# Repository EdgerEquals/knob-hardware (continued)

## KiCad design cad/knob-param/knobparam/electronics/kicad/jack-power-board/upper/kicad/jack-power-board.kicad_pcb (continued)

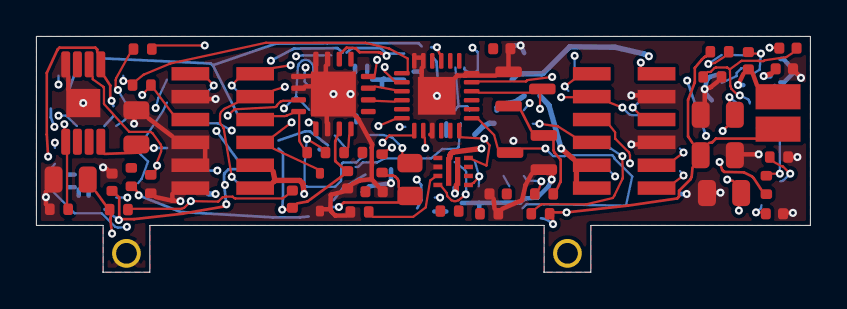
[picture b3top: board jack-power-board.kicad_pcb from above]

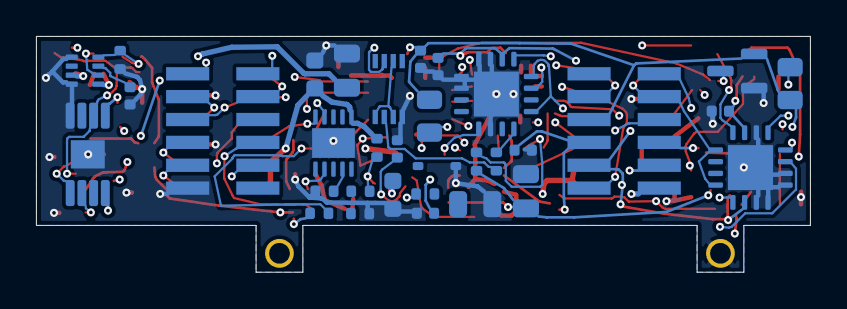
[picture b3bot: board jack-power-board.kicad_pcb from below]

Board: 4 copper layers, 43.0 x 13.1 mm, 79 parts (33 on the bottom side), 68 nets.

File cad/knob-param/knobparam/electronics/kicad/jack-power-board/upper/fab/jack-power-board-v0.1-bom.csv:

Item,Designator,Qty,Value,Footprint,Manufacturer,MPN,LCSC
1,"C20,C25",2,10nF 25V,C_0402_1005Metric,,,
2,"C22,C24",2,4.7uF 50V,C_0805_2012Metric,,,
3,"C10,C23,C27,C30",4,10uF 25V,C_0805_2012Metric,,,
4,"C21,C26,C29",3,10nF,C_0402_1005Metric,,,
5,C31,1,100nF 50V,C_0402_1005Metric,,,
6,"C32,C33",2,22uF 10V,C_0805_2012Metric,,,
7,"C53,C60",2,100nF,C_0402_1005Metric,,,
8,"C28,C54,C55,C56,C57,C58,C59",7,100nF 25V,C_0402_1005Metric,,,
9,C7,1,1nF 25V,C_0402_1005Metric,,,
10,C8,1,2.2nF,C_0402_1005Metric,,,
11,"C6,C9",2,1uF 50V,C_0603_1608Metric,,,
12,"D1,D2",2,PESD24VL1BA,D_SOD-323,,"PESD24VL1BA,115",C69324
13,"D5,D6,D7",3,BAV99,SOT-23,,BAV99,C2500
14,"H1,H2",2,PM127VS-12-12-H34,PinSocket_2x06_P1.27mm_Vertical_SMD,,PM127VS-12-12-H34-4.5-R,C2840010
15,"H3,H4",2,PZ127VS-12-12-H16,PinHeader_2x06_P1.27mm_Vertical_SMD,,PZ127VS-12-12-H16-4.5-R,C2840009
16,L2,1,2.2uH 1A,L_Cenker_CKCS252012,,,
17,R13,1,95.3k 0.5%,R_0402_1005Metric,,,
18,"R14,R16",2,10.0k 0.5%,R_0402_1005Metric,,,
19,R15,1,93.1k 0.5%,R_0402_1005Metric,,,
20,R17,1,30.9k,R_0402_1005Metric,,,
21,R2,1,14.0k,R_0402_1005Metric,,,
22,R3,1,22.6k,R_0402_1005Metric,,,
23,R4,1,102k,R_0402_1005Metric,,,
24,"R43,R45,R47",3,10R,R_0402_1005Metric,,,
25,"R44,R46,R48",3,33R 0.5W,R_0805_2012Metric,,,
26,"R49,R51,R53,R58,R59",5,100k,R_0402_1005Metric,,,
27,R5,1,30.1k,R_0402_1005Metric,,,
28,"R50,R52,R54",3,470k,R_0402_1005Metric,,,
29,"R55,R56",2,4.7k,R_0402_1005Metric,,,
30,"R18,R6",2,10.0k,R_0402_1005Metric,,,
31,"R57,R60",2,10k,R_0402_1005Metric,,,
32,R7,1,1.00k,R_0402_1005Metric,,,
33,U1,1,HUSB238_002DD,DFN-10-1EP_3x3mm_P0.5mm_EP1.65x2.38mm,,HUSB238_002DD,C7471904
34,U10,1,SN74LVC3G07DCUR,VSSOP-8_2.3x2mm_P0.5mm,,SN74LVC3G07DCUR,C131955
35,"U11,U12,U13",3,TMUX7212RUMR,QFN-16-1EP_4x4mm_P0.65mm_EP2.5x2.5mm,,TMUX7212RUMR,C3657300
36,U14,1,TCA9535RGER,Texas_RGE0024C_VQFN-24-1EP_4x4mm_P0.5mm_EP2.1x2.1mm,,TCA9535RGER,C527428
37,U2,1,TPS259470ARPWR,TI_RPW0010A_VQFN-HR-10_2x2_PLACEHOLDER,,TPS259470ARPWR,C3662799
38,U4,1,TPS7A4901DGNR,HVSSOP-8-1EP_3x3mm_P0.65mm_EP1.57x1.89mm,,TPS7A4901DGNR,C16430
39,U5,1,TPS7A3001DGNR,HVSSOP-8-1EP_3x3mm_P0.65mm_EP1.57x1.89mm,,TPS7A3001DGNR,C33835
40,U6,1,TPS62933FDRLR,SOT-583-8,,TPS62933FDRLR,C5219272

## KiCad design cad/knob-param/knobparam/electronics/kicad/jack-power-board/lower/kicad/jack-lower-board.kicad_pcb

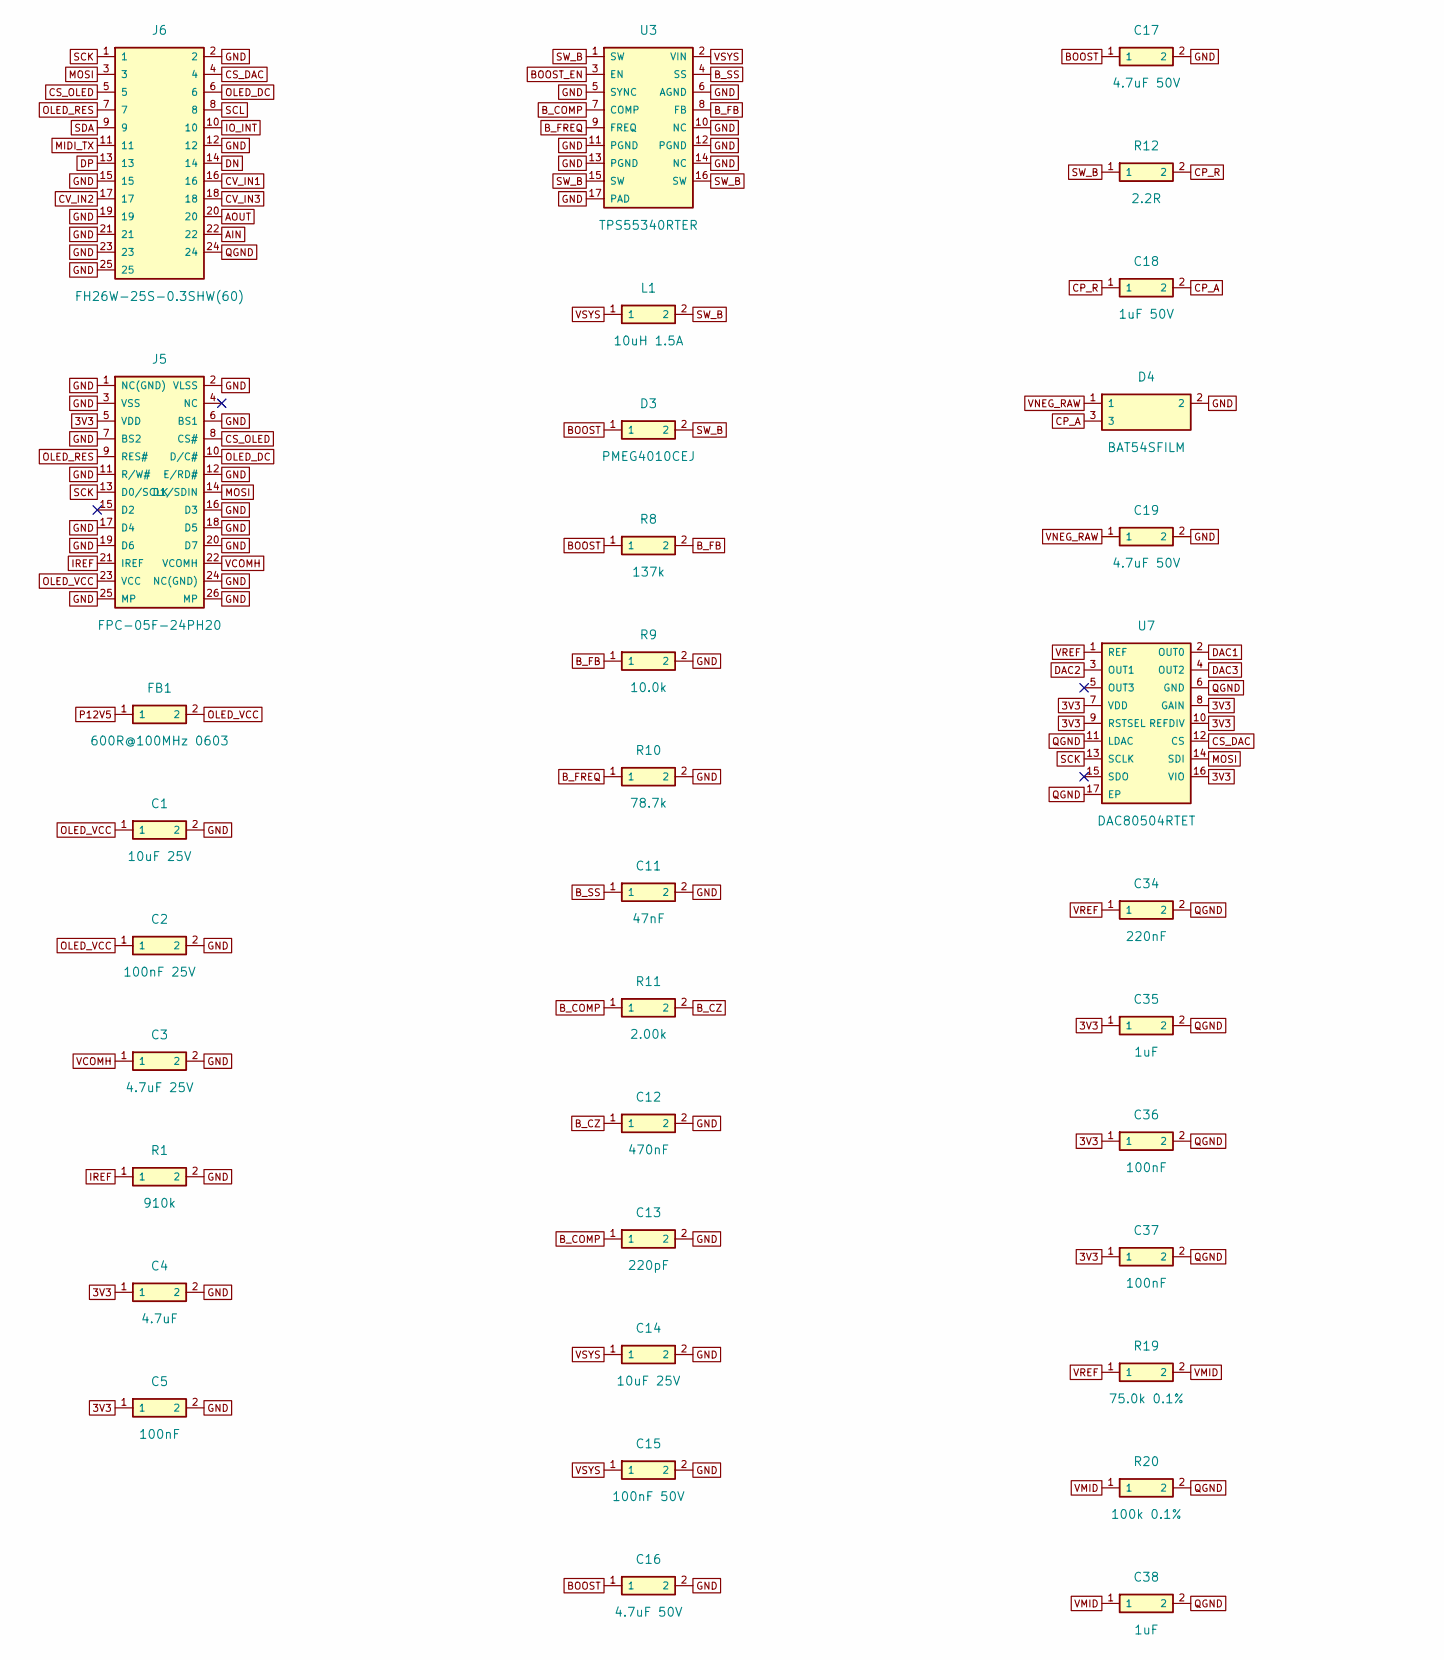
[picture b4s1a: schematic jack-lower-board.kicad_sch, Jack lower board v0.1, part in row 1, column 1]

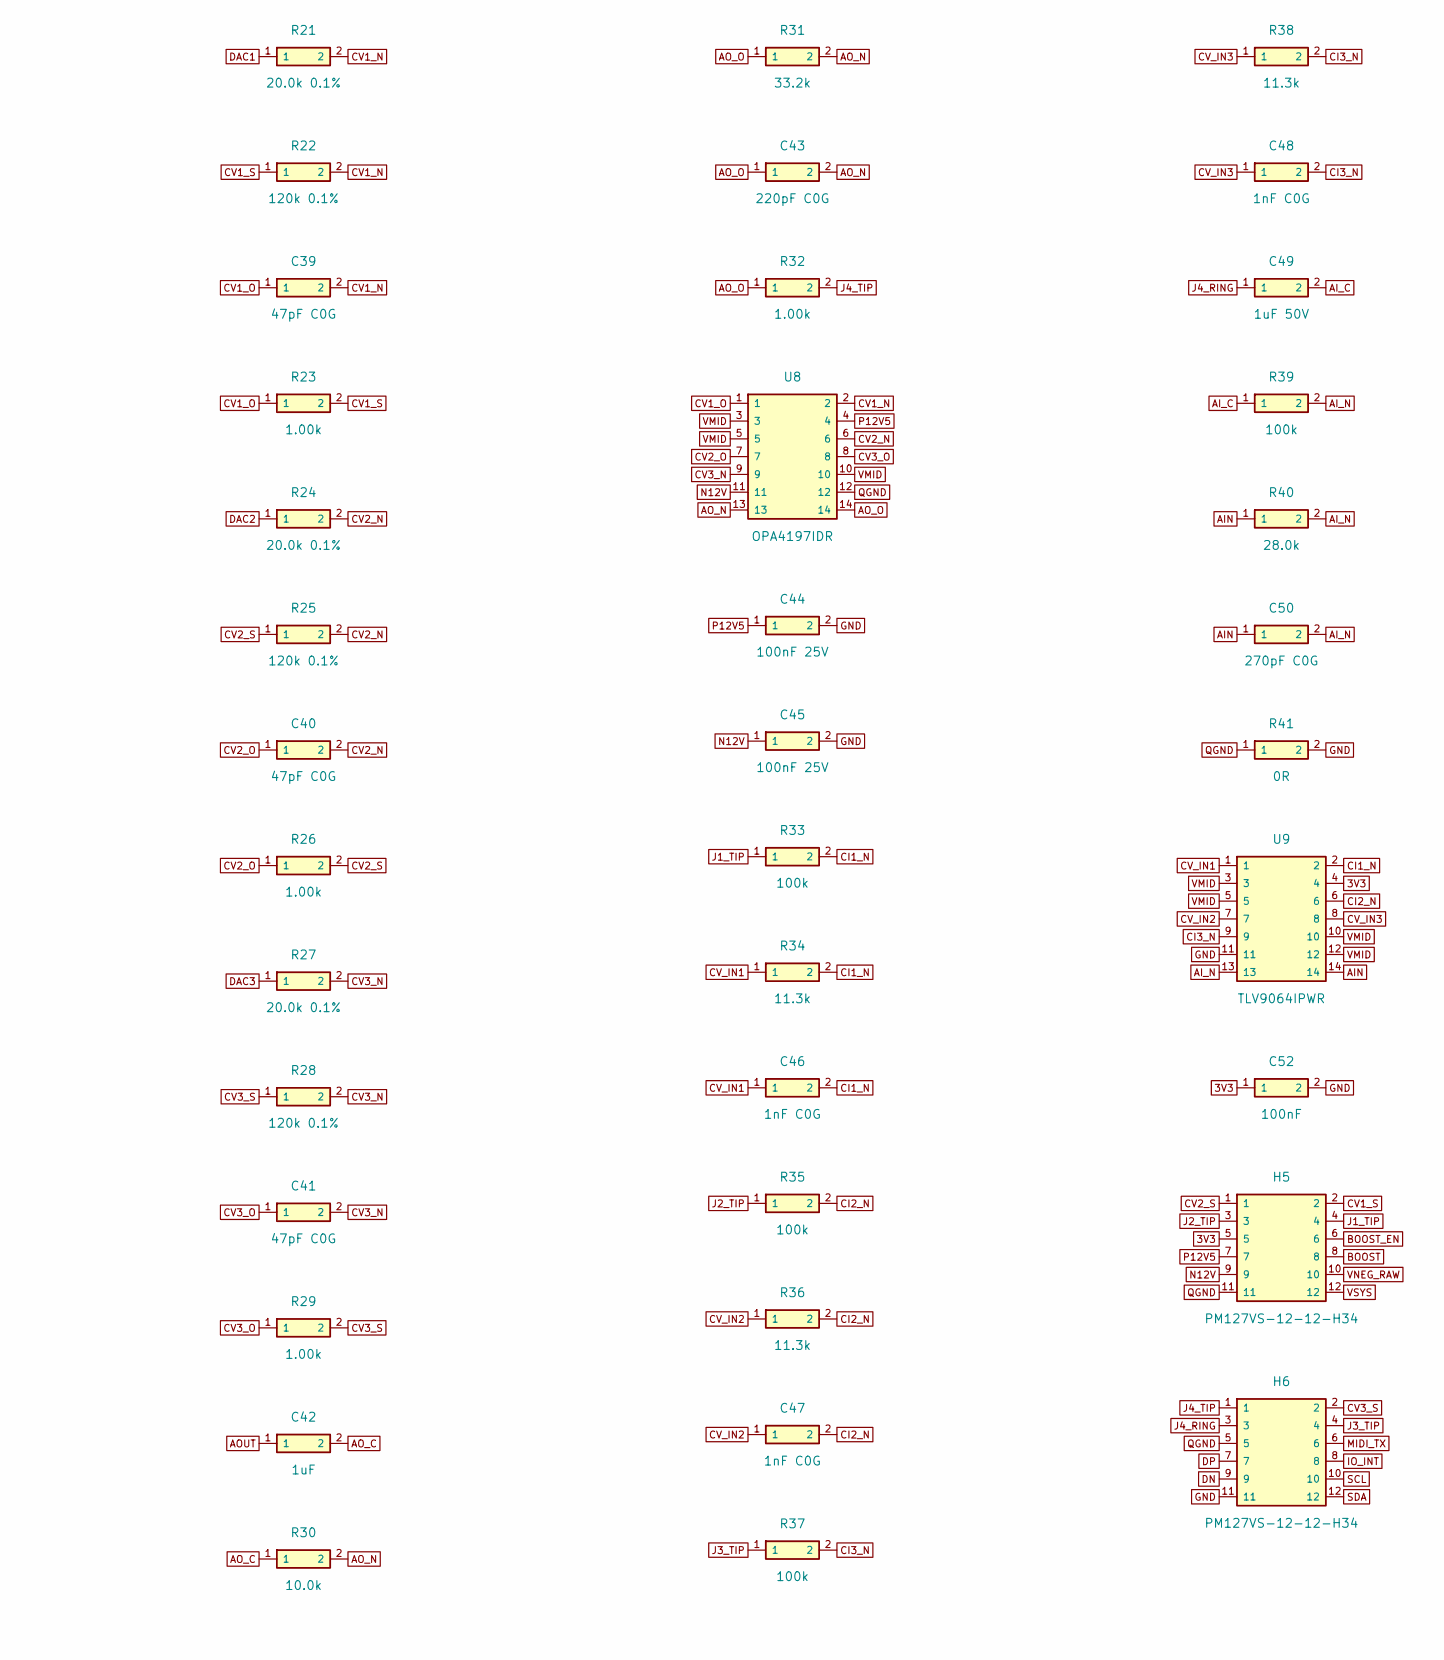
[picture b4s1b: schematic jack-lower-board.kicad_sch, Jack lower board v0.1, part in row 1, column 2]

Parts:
C1, C14: 10uF 25V; C_0805_2012Metric
C2, C44, C45: 100nF 25V; C_0402_1005Metric
C3: 4.7uF 25V; C_0805_2012Metric
C4: 4.7uF; C_0603_1608Metric
C5, C36, C37, C52: 100nF; C_0402_1005Metric
C11: 47nF; C_0402_1005Metric
C12: 470nF; C_0402_1005Metric
C13: 220pF; C_0402_1005Metric
C15: 100nF 50V; C_0402_1005Metric
C16, C17, C19: 4.7uF 50V; C_0805_2012Metric
C18, C49: 1uF 50V; C_0603_1608Metric
C34: 220nF; C_0402_1005Metric
C35, C38, C42: 1uF; C_0402_1005Metric
C39, C40, C41: 47pF C0G; C_0402_1005Metric
C43: 220pF C0G; C_0402_1005Metric
C46, C47, C48: 1nF C0G; C_0402_1005Metric
C50: 270pF C0G; C_0402_1005Metric
D3: PMEG4010CEJ; D_SOD-323F; MPN PMEG4010CEJ,115; LCSC C50704
D4: BAT54SFILM; SOT-23; MPN BAT54SFILM; LCSC C377935
FB1: 600R@100MHz 0603; L_0603_1608Metric
H5, H6: PM127VS-12-12-H34; PinSocket_2x06_P1.27mm_Vertical_SMD; MPN PM127VS-12-12-H34-4.5-R; LCSC C2840010
J5: FPC-05F-24PH20; XUNPU_FPC-05F-24PH20; MPN FPC-05F-24PH20; LCSC C2856805
J6: FH26W-25S-0.3SHW(60); Hirose_FH26-25S-0.3SHW_2Rows-25Pins-1MP_P0.60mm_Horizontal; MPN FH26W-25S-0.3SHW(60); LCSC C2904698
L1: 10uH 1.5A; L_Cenker_CKCS4020
R1: 910k; R_0402_1005Metric
R8: 137k; R_0402_1005Metric
R9, R30: 10.0k; R_0402_1005Metric
R10: 78.7k; R_0402_1005Metric
R11: 2.00k; R_0402_1005Metric
R12: 2.2R; R_0603_1608Metric
R19: 75.0k 0.1%; R_0402_1005Metric
R20: 100k 0.1%; R_0402_1005Metric
R21, R24, R27: 20.0k 0.1%; R_0402_1005Metric
R22, R25, R28: 120k 0.1%; R_0402_1005Metric
R23, R26, R29, R32: 1.00k; R_0402_1005Metric
R31: 33.2k; R_0402_1005Metric
R33, R35, R37, R39: 100k; R_0402_1005Metric
R34, R36, R38: 11.3k; R_0402_1005Metric
R40: 28.0k; R_0402_1005Metric
R41: 0R; R_0402_1005Metric
U3: TPS55340RTER; QFN-16-1EP_3x3mm_P0.5mm_EP1.7x1.7mm; MPN TPS55340RTER; LCSC C169167
U7: DAC80504RTET; QFN-16-1EP_3x3mm_P0.5mm_EP1.7x1.7mm; MPN DAC80504RTET; LCSC C2862796
U8: OPA4197IDR; SOIC-14_3.9x8.7mm_P1.27mm; MPN OPA4197IDR; LCSC C2058532
U9: TLV9064IPWR; TSSOP-14_4.4x5mm_P0.65mm; MPN TLV9064IPWR; LCSC C779410

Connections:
3V3: C4.1, C5.1, C35.1, C36.1, C37.1, C52.1, H5.5, J5.5 (VDD), U7.7 (VDD), U7.8 (GAIN), U7.9 (RSTSEL), U7.10 (REFDIV), U7.16 (VIO), U9.4
AIN: C50.1, J6.22, R40.1, U9.14
AI_C: C49.2, R39.1
AI_N: C50.2, R39.2, R40.2, U9.13
AOUT: C42.1, J6.20
AO_C: C42.2, R30.1
AO_N: C43.2, R30.2, R31.2, U8.13
AO_O: C43.1, R31.1, R32.1, U8.14
BOOST: C16.1, C17.1, D3.1, H5.8, R8.1
BOOST_EN: H5.6, U3.3 (EN)
B_COMP: C13.1, R11.1, U3.7 (COMP)
B_CZ: C12.1, R11.2
B_FB: R8.2, R9.1, U3.8 (FB)
B_FREQ: R10.1, U3.9 (FREQ)
B_SS: C11.1, U3.4 (SS)
CI1_N: C46.2, R33.2, R34.2, U9.2
CI2_N: C47.2, R35.2, R36.2, U9.6
CI3_N: C48.2, R37.2, R38.2, U9.9
CP_A: C18.2, D4.3
CP_R: C18.1, R12.2
CS_DAC: J6.4, U7.12 (CS)
CS_OLED: J5.8 (CS#), J6.5
CV1_N: C39.2, R21.2, R22.2, U8.2
CV1_O: C39.1, R23.1, U8.1
CV1_S: H5.2, R22.1, R23.2
CV2_N: C40.2, R24.2, R25.2, U8.6
CV2_O: C40.1, R26.1, U8.7
CV2_S: H5.1, R25.1, R26.2
CV3_N: C41.2, R27.2, R28.2, U8.9
CV3_O: C41.1, R29.1, U8.8
CV3_S: H6.2, R28.1, R29.2
CV_IN1: C46.1, J6.16, R34.1, U9.1
CV_IN2: C47.1, J6.17, R36.1, U9.7
CV_IN3: C48.1, J6.18, R38.1, U9.8
DAC1: R21.1, U7.2 (OUT0)
DAC2: R24.1, U7.3 (OUT1)
DAC3: R27.1, U7.4 (OUT2)
DN: H6.9, J6.14
DP: H6.7, J6.13
GND: C1.2, C2.2, C3.2, C4.2, C5.2, C11.2, C12.2, C13.2, C14.2, C15.2, C16.2, C17.2, C19.2, C44.2, C45.2, C52.2, D4.2, H6.11, J5.1 (NC(GND)), J5.2 (VLSS), J5.3 (VSS), J5.6 (BS1), J5.7 (BS2), J5.11 (R/W#), J5.12 (E/RD#), J5.16 (D3), J5.17 (D4), J5.18 (D5), J5.19 (D6), J5.20 (D7), J5.24 (NC(GND)), J5.25 (MP), J5.26 (MP), J6.2, J6.12, J6.15, J6.19, J6.21, J6.23, J6.25, R1.2, R9.2, R10.2, R41.2, U3.5 (SYNC), U3.6 (AGND), U3.10 (NC), U3.11 (PGND), U3.12 (PGND), U3.13 (PGND), U3.14 (NC), U3.17 (PAD), U9.11
IO_INT: H6.8, J6.10
IREF: J5.21 (IREF), R1.1
J1_TIP: H5.4, R33.1
J2_TIP: H5.3, R35.1
J3_TIP: H6.4, R37.1
J4_RING: C49.1, H6.3
J4_TIP: H6.1, R32.2
MIDI_TX: H6.6, J6.11
MOSI: J5.14 (D1/SDIN), J6.3, U7.14 (SDI)
N12V: C45.1, H5.9, U8.11
OLED_DC: J5.10 (D/C#), J6.6
OLED_RES: J5.9 (RES#), J6.7
OLED_VCC: C1.1, C2.1, FB1.2, J5.23 (VCC)
P12V5: C44.1, FB1.1, H5.7, U8.4
QGND: C34.2, C35.2, C36.2, C37.2, C38.2, H5.11, H6.5, J6.24, R20.2, R41.1, U7.6 (GND), U7.11 (LDAC), U7.17 (EP), U8.12
SCK: J5.13 (D0/SCLK), J6.1, U7.13 (SCLK)
SCL: H6.10, J6.8
SDA: H6.12, J6.9
SW_B: D3.2, L1.2, R12.1, U3.1 (SW), U3.15 (SW), U3.16 (SW)
VCOMH: C3.1, J5.22 (VCOMH)
VMID: C38.1, R19.2, R20.1, U8.3, U8.5, U8.10, U9.3, U9.5, U9.10, U9.12
VNEG_RAW: C19.1, D4.1, H5.10
VREF: C34.1, R19.1, U7.1 (REF)
VSYS: C14.1, C15.1, H5.12, L1.1, U3.2 (VIN)

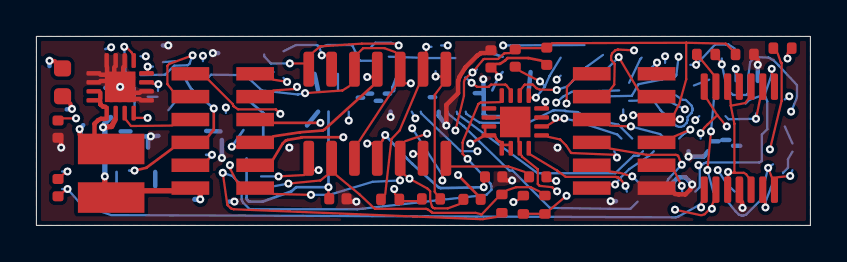
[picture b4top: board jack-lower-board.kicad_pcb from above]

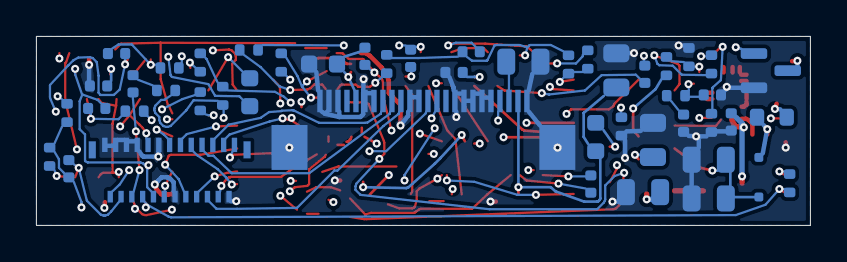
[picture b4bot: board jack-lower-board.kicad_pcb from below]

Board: 4 copper layers, 43.0 x 10.5 mm, 73 parts (48 on the bottom side), 64 nets.

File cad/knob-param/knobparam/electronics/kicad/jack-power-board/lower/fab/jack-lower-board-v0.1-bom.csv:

Item,Designator,Qty,Value,Footprint,Manufacturer,MPN,LCSC
1,"C1,C14",2,10uF 25V,C_0805_2012Metric,,,
2,C11,1,47nF,C_0402_1005Metric,,,
3,C12,1,470nF,C_0402_1005Metric,,,
4,C13,1,220pF,C_0402_1005Metric,,,
5,C15,1,100nF 50V,C_0402_1005Metric,,,
6,"C16,C17,C19",3,4.7uF 50V,C_0805_2012Metric,,,
7,"C18,C49",2,1uF 50V,C_0603_1608Metric,,,
8,C3,1,4.7uF 25V,C_0805_2012Metric,,,
9,C34,1,220nF,C_0402_1005Metric,,,
10,"C35,C38,C42,C51",4,1uF,C_0402_1005Metric,,,
11,"C36,C37,C5,C52",4,100nF,C_0402_1005Metric,,,
12,C4,1,4.7uF,C_0603_1608Metric,,,
13,"C39,C40,C41",3,47pF C0G,C_0402_1005Metric,,,
14,"C43,C50",2,220pF C0G,C_0402_1005Metric,,,
15,"C2,C44,C45",3,100nF 25V,C_0402_1005Metric,,,
16,"C46,C47,C48",3,1nF C0G,C_0402_1005Metric,,,
17,D3,1,PMEG4010CEJ,D_SOD-323F,,"PMEG4010CEJ,115",C50704
18,D4,1,BAT54SFILM,SOT-23,,BAT54SFILM,C377935
19,FB1,1,600R@100MHz 0603,L_0603_1608Metric,,,
20,"H5,H6",2,PM127VS-12-12-H34,PinSocket_2x06_P1.27mm_Vertical_SMD,,PM127VS-12-12-H34-4.5-R,C2840010
21,J5,1,FPC-05F-24PH20,XUNPU_FPC-05F-24PH20,,FPC-05F-24PH20,C2856805
22,J6,1,FH26W-25S-0.3SHW(60),Hirose_FH26-25S-0.3SHW_2Rows-25Pins-1MP_P0.60mm_Horizontal,,FH26W-25S-0.3SHW(60),C2904698
23,L1,1,10uH 1.5A,L_Cenker_CKCS4020,,,
24,R1,1,910k,R_0402_1005Metric,,,
25,R10,1,78.7k,R_0402_1005Metric,,,
26,R11,1,2.00k,R_0402_1005Metric,,,
27,R12,1,2.2R,R_0603_1608Metric,,,
28,R19,1,75.0k 0.1%,R_0402_1005Metric,,,
29,R20,1,100k 0.1%,R_0402_1005Metric,,,
30,"R22,R25,R28",3,120k 0.1%,R_0402_1005Metric,,,
31,"R21,R24,R27",3,20.0k 0.1%,R_0402_1005Metric,,,
32,"R23,R26,R29,R32",4,1.00k,R_0402_1005Metric,,,
33,R31,1,30.1k,R_0402_1005Metric,,,
34,"R34,R36,R38",3,13.3k,R_0402_1005Metric,,,
35,"R33,R35,R37,R39",4,100k,R_0402_1005Metric,,,
36,R40,1,33.0k,R_0402_1005Metric,,,
37,"R30,R41,R42,R9",4,10.0k,R_0402_1005Metric,,,
38,R8,1,137k,R_0402_1005Metric,,,
39,U3,1,TPS55340RTER,QFN-16-1EP_3x3mm_P0.5mm_EP1.7x1.7mm,,TPS55340RTER,C169167
40,U7,1,DAC80504RTET,QFN-16-1EP_3x3mm_P0.5mm_EP1.7x1.7mm,,DAC80504RTET,C2862796
41,U8,1,OPA4197IDR,SOIC-14_3.9x8.7mm_P1.27mm,,OPA4197IDR,C2058532
42,U9,1,TLV9064IPWR,TSSOP-14_4.4x5mm_P0.65mm,,TLV9064IPWR,C779410

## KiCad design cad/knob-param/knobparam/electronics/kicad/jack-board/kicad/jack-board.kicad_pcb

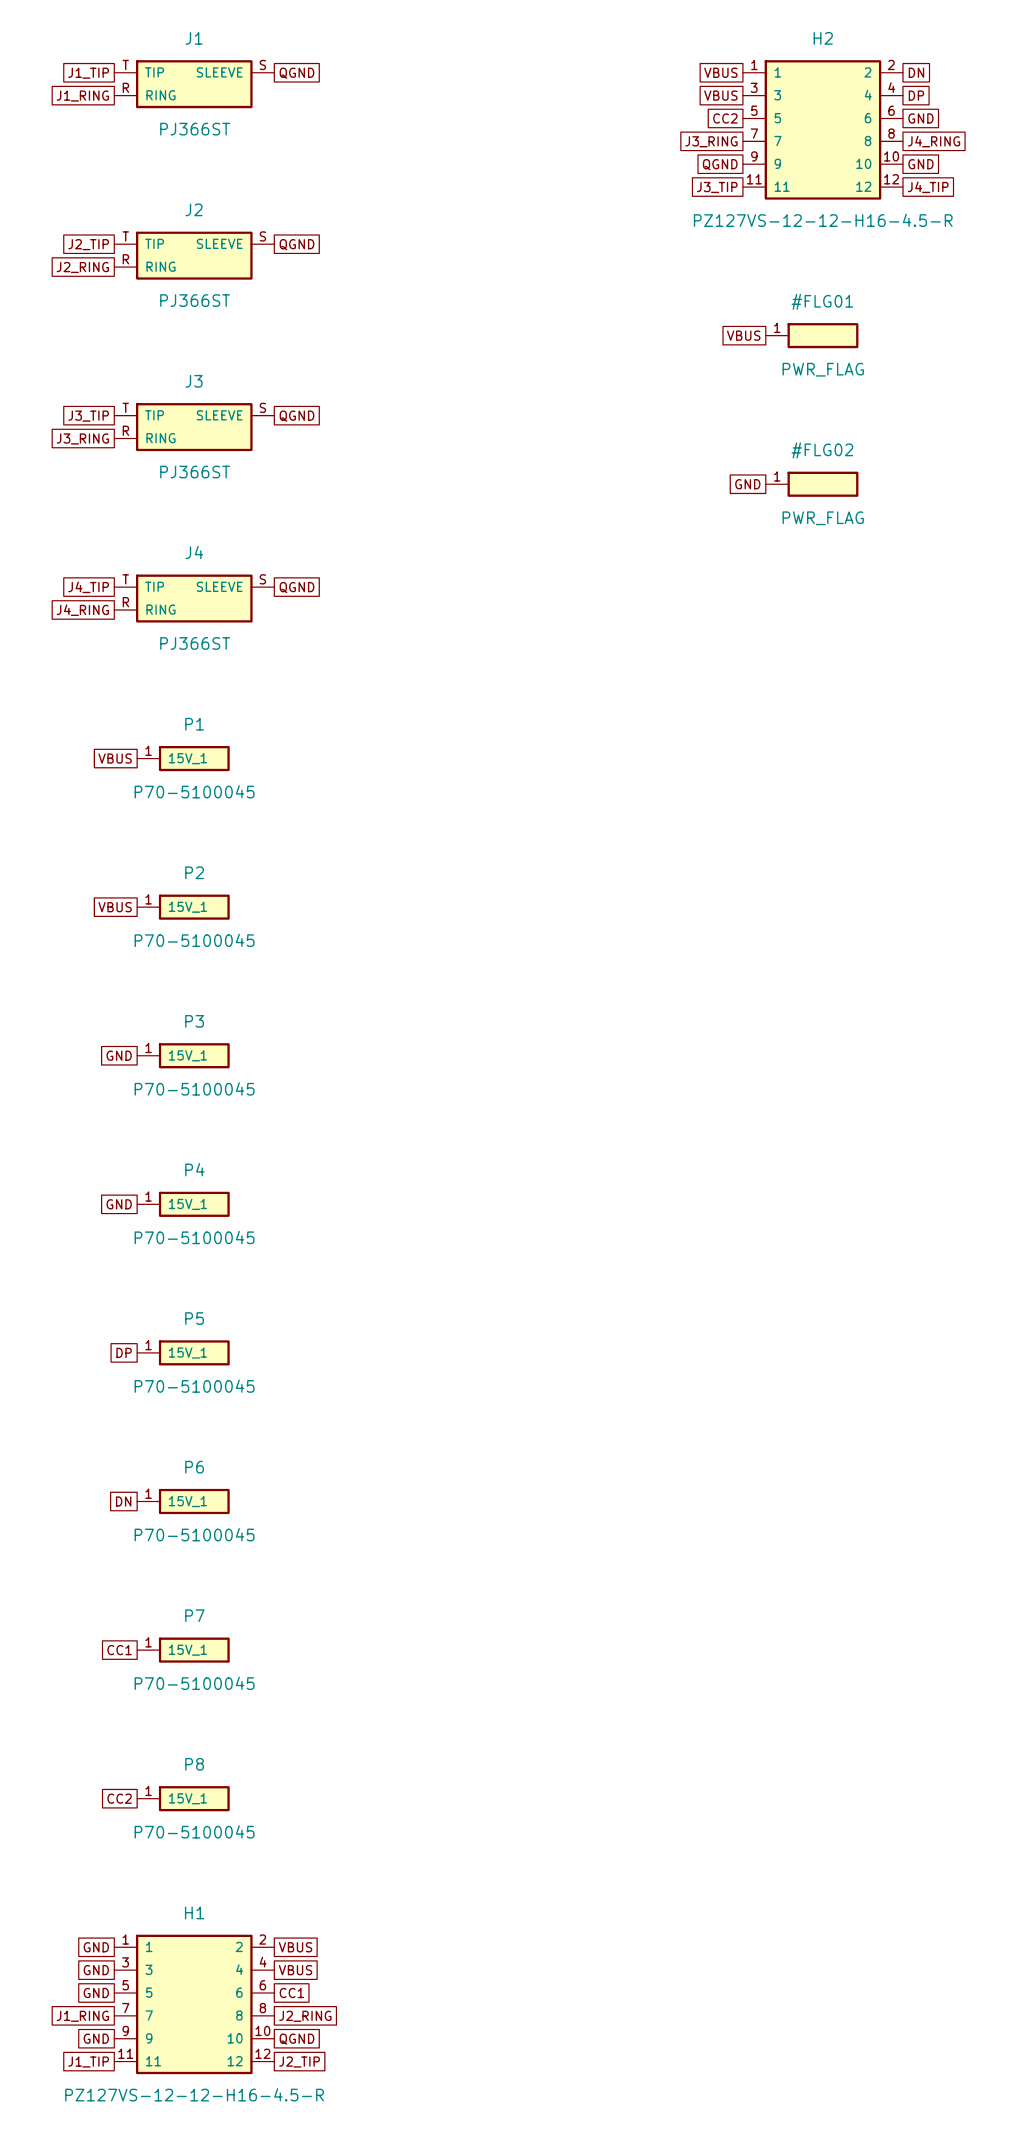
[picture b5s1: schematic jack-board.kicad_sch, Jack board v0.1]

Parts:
H1, H2: PZ127VS-12-12-H16-4.5-R; PinHeader_2x06_P1.27mm_Vertical_SMD; MPN PZ127VS-12-12-H16-4.5-R; LCSC C2840009
J1, J2, J3, J4: PJ366ST; PJ366ST_Slots; MPN PJ366ST
P1, P2, P3, P4, P5, P6, P7, P8: P70-5100045; Harwin_P70-5100045; MPN P70-5100045; LCSC C21675240

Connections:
CC1: H1.6, P7.1
CC2: H2.5, P8.1
DN: H2.2, P6.1
DP: H2.4, P5.1
GND: H1.1, H1.3, H1.5, H1.9, H2.6, H2.10, P3.1, P4.1
J1_RING: H1.7, J1.R (RING)
J1_TIP: H1.11, J1.T (TIP)
J2_RING: H1.8, J2.R (RING)
J2_TIP: H1.12, J2.T (TIP)
J3_RING: H2.7, J3.R (RING)
J3_TIP: H2.11, J3.T (TIP)
J4_RING: H2.8, J4.R (RING)
J4_TIP: H2.12, J4.T (TIP)
QGND: H1.10, H2.9, J1.S (SLEEVE), J2.S (SLEEVE), J3.S (SLEEVE), J4.S (SLEEVE)
VBUS: H1.2, H1.4, H2.1, H2.3, P1.1, P2.1

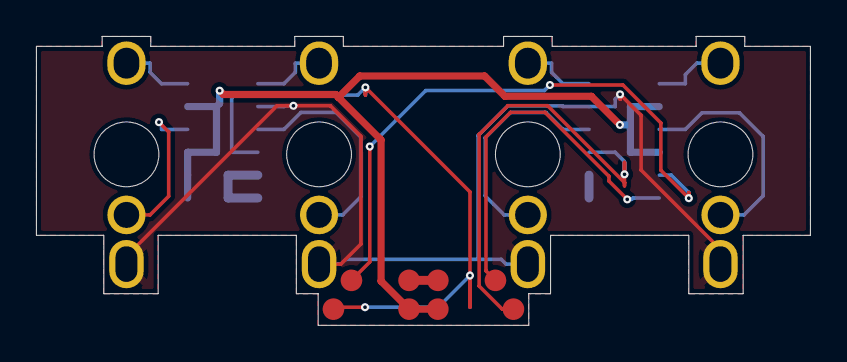
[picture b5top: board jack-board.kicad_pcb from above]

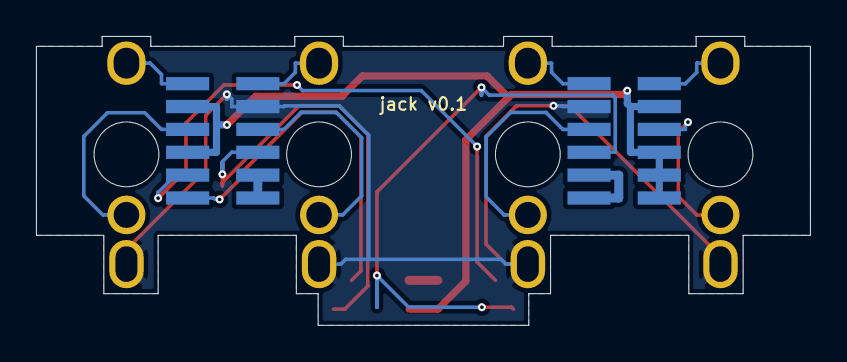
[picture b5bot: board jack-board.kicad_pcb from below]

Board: 2 copper layers, 43.0 x 16.0 mm, 14 parts (2 on the bottom side), 15 nets.

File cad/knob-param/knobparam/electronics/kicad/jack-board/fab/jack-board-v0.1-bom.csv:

Item,Designator,Qty,Value,Footprint,Manufacturer,MPN,LCSC
1,"H1,H2",2,PZ127VS-12-12-H16-4.5-R,PinHeader_2x06_P1.27mm_Vertical_SMD,XFCN,PZ127VS-12-12-H16-4.5-R,C2840009
2,"J1,J2,J3,J4",4,PJ366ST,PJ366ST_Slots,Thonk,PJ366ST,
3,"P1,P2,P3,P4,P5,P6,P7,P8",8,P70-5100045,Harwin_P70-5100045,Harwin,P70-5100045,C21675240

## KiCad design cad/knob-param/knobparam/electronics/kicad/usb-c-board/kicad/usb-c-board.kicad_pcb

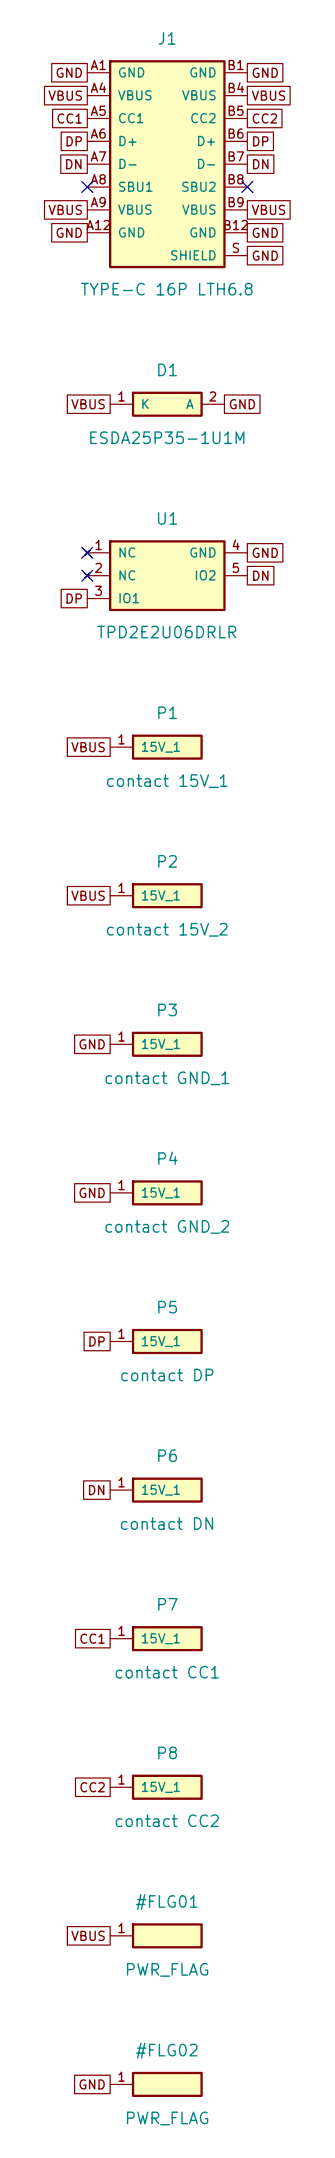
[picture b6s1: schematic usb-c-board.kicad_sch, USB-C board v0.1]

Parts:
D1: ESDA25P35-1U1M; D_DFN1610-2_ESDA25P35; MPN ESDA25P35-1U1M; LCSC C1974707
J1: TYPE-C 16P LTH6.8; USB_C_16P_Vertical_ShouHan_LTH6.8; MPN TYPE-C 16P LTH6.8; LCSC C5187468
P1: contact 15V_1; SpringContact_Landing_D1.2
P2: contact 15V_2; SpringContact_Landing_D1.2
P3: contact GND_1; SpringContact_Landing_D1.2
P4: contact GND_2; SpringContact_Landing_D1.2
P5: contact DP; SpringContact_Landing_D1.2
P6: contact DN; SpringContact_Landing_D1.2
P7: contact CC1; SpringContact_Landing_D1.2
P8: contact CC2; SpringContact_Landing_D1.2
U1: TPD2E2U06DRLR; SOT-553; MPN TPD2E2U06DRLR; LCSC C1972959

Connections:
CC1: J1.A5 (CC1), P7.1
CC2: J1.B5 (CC2), P8.1
DN: J1.A7 (D-), J1.B7 (D-), P6.1, U1.5 (IO2)
DP: J1.A6 (D+), J1.B6 (D+), P5.1, U1.3 (IO1)
GND: D1.2 (A), J1.A1 (GND), J1.A12 (GND), J1.B1 (GND), J1.B12 (GND), J1.S (SHIELD), P3.1, P4.1, U1.4 (GND)
VBUS: D1.1 (K), J1.A4 (VBUS), J1.A9 (VBUS), J1.B4 (VBUS), J1.B9 (VBUS), P1.1, P2.1

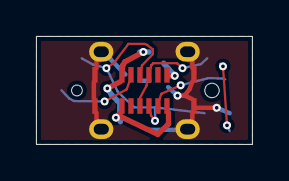
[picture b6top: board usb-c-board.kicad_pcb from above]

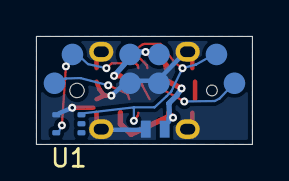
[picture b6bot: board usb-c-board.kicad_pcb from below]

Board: 2 copper layers, 12.0 x 6.0 mm, 11 parts (10 on the bottom side), 6 nets.

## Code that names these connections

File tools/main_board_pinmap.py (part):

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    G.append(("back AMOLEDs shared reset and power enable", "gpio", [""], [("AM_RESX", []), ("AM_PWR_EN", [])], None))
    G.append(("link flex SPI (jack lower board: DAC80504, clear OLED)", "inst", SPIS,
              [("LINK_SCK", ["{i}_SCK"]), ("LINK_MOSI", ["{i}_MOSI"])], "SPI"))
    G.append(("link flex chip selects and OLED lines", "gpio", [""], [("CS_DAC", []), ("CS_OLED", []), ("OLED_DC", []), ("OLED_RES", [])], None))
    G.append(("I2C (TMAG5273, the jack unit's TCA9535 over the link; one bus [A])", "inst", ["I2C1", "I2C2", "I2C3", "I2C4"],
              [("I2C_SCL", ["{i}_SCL"]), ("I2C_SDA", ["{i}_SDA"])], "I2C"))
    G.append(("interrupts", "gpio", [""], [("IO_INT*", []), ("HALL3D_INT*", [])], None))
    G.append(("MIDI out (link)", "inst", UARTS, [("MIDI_TX", ["{i}_TX"])], "UART"))
    # [Ed 8 Nov Q43 = A] the rod link is a bias tee with a Manchester code (about 2 Mbit/s): one timer sends (PWM / DMA) and
    # times the received edges (input capture / DMA)
    G.append(("dial link through the rod (Manchester on the rod's 5 V, one timer + DMA)", "inst", TIMS,
              [("DIAL_TX", ["{i}_CH1", "{i}_CH3"]), ("DIAL_RX", ["{i}_CH2", "{i}_CH4"])], "TIM"))
    # [A] OTG_FS on PA11 / PA12 only (8 Nov, step 3): the H74x ROM bootloader's USB DFU uses those pins [C AN2606], and the
    # field update path counts on it; the step-3 re-solve had moved USB to OTG_HS's PB14 / PB15
    G.append(("USB (link flex, FS on the internal PHY)", "fixed", [""], [("USB_DM", ["USB_OTG_FS_DM"]), ("USB_DP", ["USB_OTG_FS_DP"])], None))
    G.append(("CAN (vertical board R's transceiver)", "inst", ["FDCAN1", "FDCAN2"], [("CAN_TX", ["{i}_TX"]), ("CAN_RX", ["{i}_RX"])], "FDCAN"))
    G.append(("CAN standby", "gpio", [""], [("CAN_STBY", [])], None))
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              [("ENC_A", ["{i}_CH1"]), ("ENC_B", ["{i}_CH2"])], "TIM"))
    G.append(("1220 driver PWM (IN1, IN2)", "inst", TIMS, [("MOT_IN1", ["{i}_CH1", "{i}_CH3"]), ("MOT_IN2", ["{i}_CH2", "{i}_CH4"])], "TIM"))
    # [S TI DRV8213 DSG] the DSG package has no nSLEEP pin (it sleeps itself when IN1 = IN2 = 0) and VREF is fixed inside
    G.append(("Hall enable", "gpio", [""], [("HALL_EN", [])], None))
    # [Ed 8 Nov Q35 / Q36 = B] the ring's VCSELs and their decoder are gone; one red VCSEL is the power light, one transistor, PWM
    G.append(("power light VCSEL (PWM, one transistor)", "inst", TIMS, [("PWR_LIGHT", ["{i}_CH1", "{i}_CH2", "{i}_CH3", "{i}_CH4"])], "TIM"))
    G.append(("RGB ring data (timer + DMA)", "inst", TIMS, [("RGB_DIN", ["{i}_CH1", "{i}_CH2", "{i}_CH3", "{i}_CH4"])], "TIM"))
    # the violet source is on the dial board, run by the dial's own chip over the rod link: no main-chip pin
    G.append(("RGB ring power switch", "gpio", [""], [("RGB_EN", [])], None))
    G.append(("Risley motors (PWM, later) [A reserved]", "inst", TIMS,
              [("RISLEY1", ["{i}_CH1", "{i}_CH3"]), ("RISLEY2", ["{i}_CH2", "{i}_CH4"])], "TIM"))
    G.append(("joystick screen reset, TE, power", "gpio", [""], [("JOY_RST", []), ("JOY_TE*", []), ("JOY_PWR_EN", [])], None))
    G.append(("15 V present", "gpio", [""], [("BUS_PRESENT", [])], None))
    G.append(("5 V on (board L's 5 V buck enable) [Ed Q38 = A]", "gpio", [""], [("5V_EN", [])], None))
    G.append(("crystal", "fixed", [""], [("HSE_IN", ["RCC_OSC_IN"]), ("HSE_OUT", ["RCC_OSC_OUT"])], None))
    G.append(("debug (SWD + SWO)", "fixed", [""], [("SWDIO", ["DEBUG_JTMS-SWDIO"]), ("SWCLK", ["DEBUG_JTCK-SWCLK"]), ("SWO", ["DEBUG_JTDO-SWO"])], None))
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
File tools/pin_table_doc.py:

"""Rewrite the H743 pin table in docs/main-board-circuit-2026-11-07.md from the pin map json (after each re-solve).
  python3 tools/pin_table_doc.py"""
import json, os

ROOT = os.path.dirname(os.path.dirname(os.path.abspath(__file__)))
J = json.load(open(os.path.join(ROOT, "cad/knob-param/knobparam/electronics/kicad/knob-main-pcb/pinmap/h743-lqfp100-simple.json")))
N = {n: v["pin"].split("-")[0].split(" ")[0] for n, v in J["nets"].items()}
S = {n: v["signal"] for n, v in J["nets"].items()}


def f(*ns, sig=False):
    return ", ".join(f"{n} {N[n]}" + (f" ({S[n]})" if sig else "") for n in ns)


rows = [
    ("Joystick screen, QUADSPI", f("JOY_QSPI_CLK", "JOY_QSPI_NCS", "JOY_QSPI_IO0", "JOY_QSPI_IO1", "JOY_QSPI_IO2", "JOY_QSPI_IO3").replace("JOY_QSPI_", "")
     + "; " + f("JOY_RST", "JOY_TE", "JOY_PWR_EN").replace("JOY_", "")),
    (f"Link flex {S['LINK_SCK'].split('_')[0]}", f("LINK_SCK", "LINK_MOSI").replace("LINK_", "") + "; " + f("CS_DAC", "CS_OLED", "OLED_DC", "OLED_RES")),
    (f"{S['I2C_SCL'].split('_')[0]}", f("I2C_SCL", "I2C_SDA").replace("I2C_", "") + "; " + f("IO_INT", "HALL3D_INT")),
    ("MIDI, dial link", f"MIDI_TX {N['MIDI_TX']} ({S['MIDI_TX'].split('_')[0]}); rod link [Q43 = A] DIAL_TX {N['DIAL_TX']} ({S['DIAL_TX']}), "
     f"DIAL_RX {N['DIAL_RX']} ({S['DIAL_RX']}), Manchester by timer + DMA"),
    ("USB FS", f("USB_DM", "USB_DP").replace("USB_", "") + " (OTG_FS: the ROM bootloader's USB DFU pins [C AN2606])"),
    (f"CAN ({S['CAN_TX'].split('_')[0]})", f("CAN_TX", "CAN_RX", "CAN_STBY").replace("CAN_", "")),
    ("ADC1", f("CV_IN1", "CV_IN2", "CV_IN3", "AUDIO_IN", "HALL1", "HALL2", "HALL4", "HALL5", "MOT_SENSE", "MOT_VOICE", "NTC", "JOY_LADDER")),
    ("ADC2, ground sense [Q41]", f"AGND_SENSE {N['AGND_SENSE']} ({S['AGND_SENSE']}): sampled by ADC2 at the same instant as ADC1's CV in / audio in "
     "(dual simultaneous mode), subtracted in firmware [A]"),
    ("DAC1", f("AUDIO_OUT")),
    (f"Encoder ({S['ENC_A'].split('_')[0]})", f("ENC_A", "ENC_B")),
    (f"1220 ({S['MOT_IN1'].split('_')[0]}), Halls", f("MOT_IN1", "MOT_IN2") + " (100 kHz PWM [Q39]); " + f("HALL_EN")),
    ("Power light [Q36]", f"PWR_LIGHT {N['PWR_LIGHT']} ({S['PWR_LIGHT']}, PWM into one transistor)"),
    ("RGB ring", f"RGB_DIN {N['RGB_DIN']} ({S['RGB_DIN'].split('_')[0]} + DMA), RGB_EN {N['RGB_EN']} (the ring's 5 V switch)"),
    ("Board L", f"5V_EN {N['5V_EN']} (the 5 V buck's enable; 3.3 V is always on) [Q38]"),
    ("Risley (reserved)", f"{N['RISLEY1']}, {N['RISLEY2']} ({S['RISLEY1'].split('_')[0]}), no tracks yet"),
    ("Cover board (later)", f"COVER_TX {N['COVER_TX']}, COVER_RX {N['COVER_RX']} ({S['COVER_TX'].split('_')[0]}), COVER_EN {N['COVER_EN']}"),
    ("System", f"BUS_PRESENT {N['BUS_PRESENT']}; HSE PH0 / PH1; SWDIO PA13, SWCLK PA14, SWO PB3"),
]
table = "| Group | Nets (pin) |\n|---|---|\n" + "".join(f"| {a} | {b} |\n" for a, b in rows)
p = os.path.join(ROOT, "docs/main-board-circuit-2026-11-07.md"); s = open(p).read()
i = s.index("| Group | Nets (pin) |"); j = s.index("\n## H743 core")
open(p, "w").write(s[:i] + table + s[j:])
print(table)

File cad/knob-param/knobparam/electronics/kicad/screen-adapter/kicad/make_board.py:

"""Authoring script for the round screen adapter board (KiCad is the single source of truth for this board).
Run with the system python that has pcbnew:  /usr/bin/python3 make_board.py
Writes screen-adapter.kicad_pcb / .kicad_pro / fp-lib-table, then exports ../screen-adapter.step with kicad-cli.
Contents: round Edge.Cuts outline, 2 layers, 1.0 thick [A]; footprints from the shared library (cad/library/kicad/footprints.pretty):
  J1 = FPC_14P_0.5mm_Top   for the 0.71" round TFT tail (14 pin, 0.5 pitch [A], Zhunyi Z07101-P14)
  U1 = QFN-20_3x3_P0.4_CH32V003   CH32V003F4U6 [A]
  C1 = TubeRodClamp_Adapter_M1.6   v0.2 (2026-10-31): NPTH Ø1.8 for the M1.6 rod; B.Cu ring GND on the tube top, F.Cu ring VBUS_DATA
       under the thin nut (data over power; replaces W1, the 4 wire pads)
  v0.3 (2026-10-31, Ed): U3 = SOT-23-6_TMAG5273  TI TMAG5273 3D Hall sensor (control-dial angle, magnet Ø3x1 N52 in the dial
       hub web below), I2C to U1 (PC1 SDA pin 8, PC2 SCL pin 9; VDD pin 6, VSS pin 4 [CH32V003 DS]); INT to PC3 (pin 10) [A];
       C2 100 nF 0402 decoupling at U3 VCC; R1/R2 4.7k 0402 I2C pull-ups [A]. Nets VCC [A: 3.3 V rail, regulator TBC], GND, SDA, SCL.
       Top nut is now a DIN 934 (1.3) with 3.0 cord room above (holder v0.5).
Placed only, no routing (ratsnest left for the layout). Grid origin = board centre (x right, y down in KiCad)."""
import os, json, subprocess, pcbnew

ORIGIN = (100.0, 100.0)     # KiCad position of the board centre (sheet placement only)
BOARD_D = 15.5              # [A] <= 18 (Ed); smallest round that holds J1 with 0.3 courtyard-to-edge
BOARD_T = 1.0               # [A]
J1_POS = (0.0, -3.7)        # [A] KiCad coords (y up = negative); v0.2: 0.5 out for the M1.6 nut at the centre (was -3.2)
U1_POS = (0.0, 3.8)         # [A] v0.2: was 3.5
C1_POS = (0.0, 0.0)         # centre: tube / rod clamp (v0.2 replaces the W1 wire pads)
U3_POS, U3_ROT = (5.7, 0.2), 90.0   # [A] v0.3 TMAG5273: r 5.70 from the dial axis = magnet radius in control dial v0.7
C2_POS = (3.3, 3.2)         # [A] 100 nF at U3
R1_POS, R2_POS = (-3.3, 2.6), (-3.3, 3.6)   # [A] I2C pull-ups
EDGE_CLEAR_CU = 0.3         # [A] copper to board edge (default 0.5 relaxed for the small board)

HERE = os.path.dirname(os.path.abspath(__file__))
NAME = "screen-adapter"
LIBDIR = os.path.normpath(os.path.join(HERE, "..", "..", "..", "kicad", "footprints.pretty"))
mm = pcbnew.FromMM
def P(x, y): return pcbnew.VECTOR2I(mm(ORIGIN[0] + x), mm(ORIGIN[1] + y))

board = pcbnew.BOARD()
ds = board.GetDesignSettings(); ds.SetBoardThickness(mm(BOARD_T)); ds.SetCopperLayerCount(2)
ds.m_CopperEdgeClearance = mm(EDGE_CLEAR_CU)
c = pcbnew.PCB_SHAPE(board, pcbnew.SHAPE_T_CIRCLE); c.SetLayer(pcbnew.Edge_Cuts); c.SetWidth(mm(0.05))
c.SetCenter(P(0, 0)); c.SetEnd(P(BOARD_D / 2, 0)); board.Add(c)

def place(fpname, ref, pos, back=False, rot=0.0):
    fp = pcbnew.FootprintLoad(LIBDIR, fpname); fp.SetFPID(pcbnew.LIB_ID("footprints", fpname))
    fp.SetReference(ref); fp.SetPosition(P(*pos))
    if rot: fp.SetOrientationDegrees(rot)
    board.Add(fp)   # add first, then flip (flipping an unparented footprint crashes pcbnew 9)
    if back: fp.Flip(P(*pos), pcbnew.FLIP_DIRECTION_TOP_BOTTOM)
    return fp
place("FPC_14P_0.5mm_Top", "J1", J1_POS)
u1 = place("QFN-20_3x3_P0.4_CH32V003", "U1", U1_POS)
c1 = place("TubeRodClamp_Adapter_M1.6", "C1", C1_POS)
u3 = place("SOT-23-6_TMAG5273", "U3", U3_POS, rot=U3_ROT)
c2 = place("C_0402", "C2", C2_POS); r1 = place("R_0402", "R1", R1_POS); r2 = place("R_0402", "R2", R2_POS)
for fp, v in ((u3, "TMAG5273A1"), (c2, "100n"), (r1, "4k7"), (r2, "4k7"), (u1, "CH32V003F4U6")): fp.SetValue(v)
NETS = {n: pcbnew.NETINFO_ITEM(board, n) for n in ("GND", "VBUS_DATA", "VCC", "SDA", "SCL", "HALL_INT")}   # [A]
for n in NETS.values(): board.Add(n)
def net(fp, pin, n):
    for pad in fp.Pads():
        if pad.GetNumber() == pin: pad.SetNet(NETS[n])
for pin, n in (("4", "GND"), ("6", "VCC"), ("8", "SDA"), ("9", "SCL"), ("10", "HALL_INT")): net(u1, pin, n)
for pin, n in (("1", "SCL"), ("2", "GND"), ("3", "GND"), ("4", "VCC"), ("5", "HALL_INT"), ("6", "SDA")): net(u3, pin, n)
net(c2, "1", "VCC"); net(c2, "2", "GND"); net(r1, "1", "VCC"); net(r1, "2", "SDA"); net(r2, "1", "VCC"); net(r2, "2", "SCL")
for pad in c1.Pads():
    if pad.GetNumber() == "1": pad.SetNet(NETS["GND"])         # B.Cu ring on the brass tube top
    elif pad.GetNumber() == "2": pad.SetNet(NETS["VBUS_DATA"]) # F.Cu ring under the M1.6 thin nut
ds.SetAuxOrigin(P(0, 0)); ds.SetGridOrigin(P(0, 0))

pcb_path = os.path.join(HERE, NAME + ".kicad_pcb")
pcbnew.SaveBoard(pcb_path, board)
json.dump({"meta": {"filename": NAME + ".kicad_pro", "version": 1}, "board": {"design_settings": {"rules": {"min_copper_edge_clearance": EDGE_CLEAR_CU}}}, "libraries": {}},
          open(os.path.join(HERE, NAME + ".kicad_pro"), "w"), indent=2)
open(os.path.join(HERE, "fp-lib-table"), "w").write(
    '(fp_lib_table\n  (version 7)\n  (lib (name "footprints")(type "KiCad")(uri "${KIPRJMOD}/../../../kicad/footprints.pretty")(options "")(descr "Ed project footprints"))\n)\n')
step = os.path.join(HERE, "..", NAME + ".step")
subprocess.run(["kicad-cli", "pcb", "export", "step", "--grid-origin", "--force", "-o", step, pcb_path], check=True)
print("board Ø", BOARD_D, "J1", J1_POS, "U1", U1_POS, "C1", C1_POS, "U3", U3_POS, U3_ROT, "C2", C2_POS, "R1", R1_POS, "R2", R2_POS)
